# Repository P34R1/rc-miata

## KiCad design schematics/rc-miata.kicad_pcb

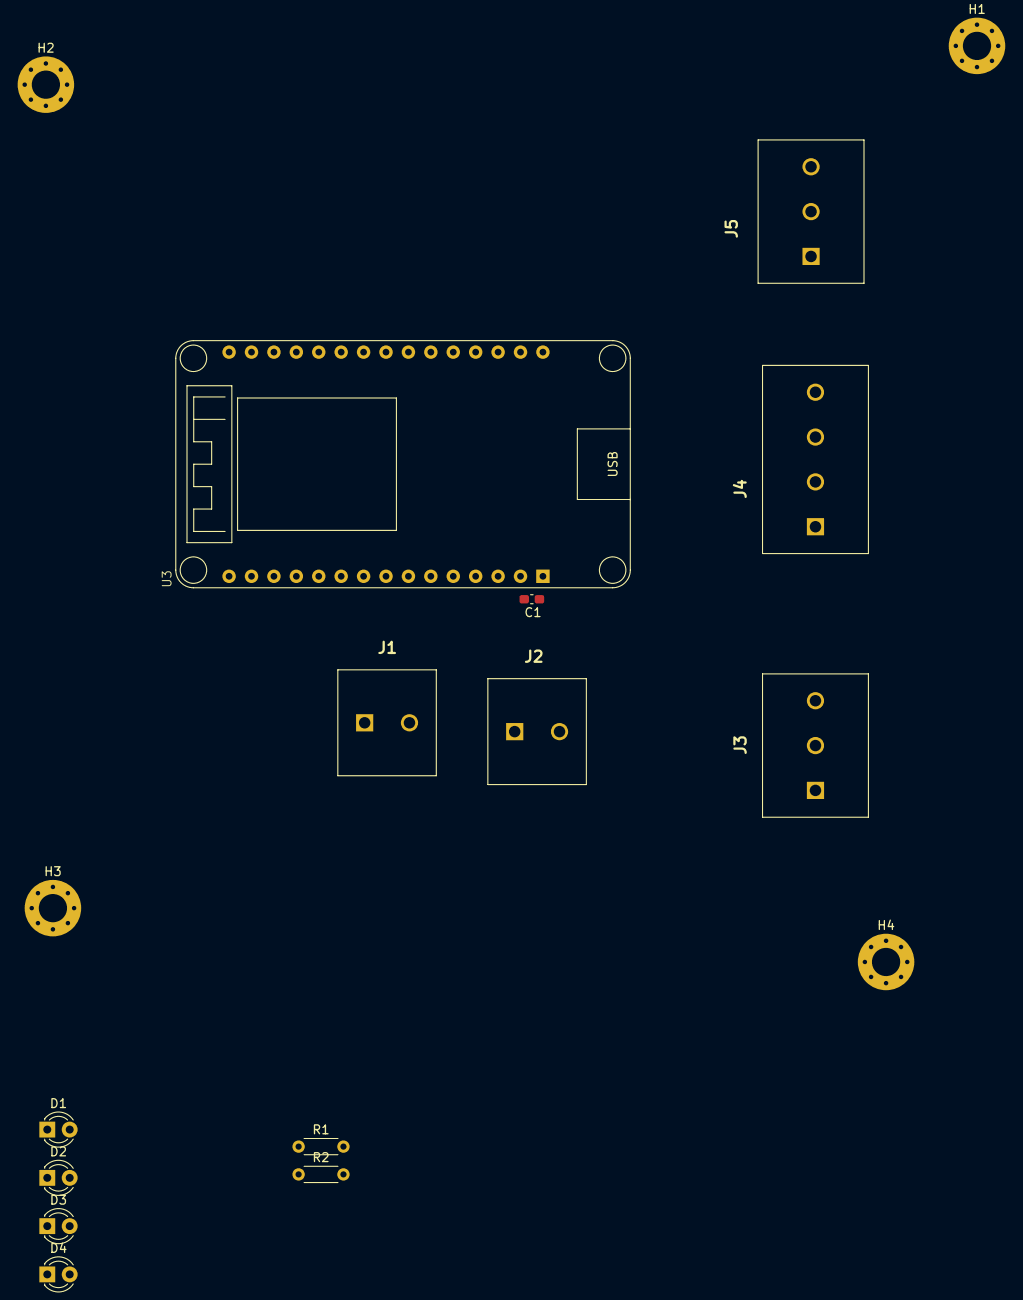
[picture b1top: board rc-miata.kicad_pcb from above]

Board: 2 copper layers, 17 parts (0 on the bottom side), 11 nets, no tracks yet.

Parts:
C1: 100n; C_0603_1608Metric_Pad1.08x0.95mm_HandSolder
D1, D2, D4: YELLOW; LED_D3.0mm
D3: RED; LED_D3.0mm
H1, H2, H3, H4: M3; MountingHole_3.2mm_M3_Pad_Via
J1: Battery; 1869211
J2: Switch; 1869211
J3: UBEC; 1161181
J4: ESC; 1869237
J5: SERVO; 1161181
R1, R2: 330; R_Axial_DIN0204_L3.6mm_D1.6mm_P5.08mm_Horizontal
U3: ESP32; ESP32 Devkitv1

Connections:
+5V: C1.1, J3.3, U3.1 (VIN)
+6V: J4.2, J5.1
/Battery +: J2.1, J3.1, J4.1
/Servo Signal: J5.3, U3.21 (IO19)
/Switch: J1.1, J2.2
ESC Signal: J4.3, U3.22 (IO18)
GND: C1.2, D1.1 (K), D2.1 (K), D3.1 (K), D4.1 (K), H1.1 (1_1), H2.1 (1_1), H3.1 (1_1), H4.1 (1_1), J1.2, J3.2, J5.2, U3.2 (GND), U3.29 (GND)
Headlight LEDs: R1.2, U3.20 (IO21)
unnamed: D1.2 (A), D2.2 (A), R1.1
unnamed: D3.2 (A), D4.2 (A), R2.1
Taillight LEDs: R2.2, U3.17 (IO22)

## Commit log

2026-05-21 initial
    temp
    esp-generate
2026-05-21 esp generate
2026-05-21 refactor wifi into src/wifi.rs
2026-05-21 rename main.rs to remote.rs
2026-05-21 setup wifi
2026-05-21 initial schematics
2026-05-21 refactor directory structure
2026-05-22 Created ESC and BDLC Symbols. Added to schematic unwired
2026-05-22 Reorganized Files
2026-05-22 fixed .history
2026-05-22 Created UBEC symbol. Added UBEC to schematic unwired
2026-05-22 Started wiring battery circuit
2026-05-22 Fixed Rev. Continued wiring. Chnaged 5.8V to 6V
2026-05-22 Added 5V to ESP
2026-05-24 Named nets. Started updating ESP32
2026-05-24 Created ESP32 Symbol. Wired ESP32
2026-05-25 Created Servo symbol. Wired servo.
2026-05-25 Added decoupling capacitor
2026-05-26 Fixed ERC Errors
2026-05-26 Added and Wired LEDs. Changed sheet to US LETTER SIZE A
2026-05-26 Added Resistors for LEDs. Value Clarity
2026-05-26 Updated Title Block
2026-06-01 Labeled Battery. Started Connectors Library
2026-06-01 Finished 2,3, and 4 Terminal Blocks Added Battery Terminal
2026-06-01 Added and wired terminal blocks to schematic
2026-06-01 Fixed pin connections for servo and UBEC
2026-06-01 Applied footprints
2026-06-01 Updated header blocks. Populated PCB title block
2026-06-01 Added no connect flags to unused pins
2026-06-02 Updated ESP-32. Added footprint for resistors and ESP-32
2026-06-02 Cleaned up schematic
2026-06-02 Set board layers
2026-06-03 Rough PCB layout. Basic board properties
2026-06-04 Updated ESP footprint
